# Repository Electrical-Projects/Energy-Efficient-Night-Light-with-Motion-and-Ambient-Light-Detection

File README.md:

## Energy-Efficient Night-Light with Motion and Ambient-Light Detection

# Description
A simple and affordable motion-activated LED circuit designed for environments where activation should depend on both motion and ambient light levels. The circuit uses a PIR motion sensor and a light-dependent resistor (LDR) to allow users to define the lighting conditions under which motion will trigger the LED. Two onboard potentiometers independently adjust: (1) the environmental light threshold (from full daylight to complete darkness) and (2) the LED on-time delay (0 – 72 seconds). The design is entirely analog, requiring no microcontroller, programming, or complex setup, making it easy to replicate and modify. The circuit is open source under GNU GPL 3.0 and may be freely used, modified, and shared.

# Overview
The system operates by combining PIR motion detection with ambient light sensing. The LDR and potentiometer form an adjustable voltage divider that biases a transistor, determining whether motion detection is enabled based on current light conditions. A TLV8544 low-power comparator stage processes the sensor signals and feeds them into a SN74LVC1G00 NAND gate for signal inversion and logic control before triggering a 555 timer configured in monostable mode. The second potentiometer adjusts the RC time constant of the 555 timer, allowing precise control over the LED on-time from near-instant to over one minute.

Most of the circuit is built with through-hole components for ease of assembly, modification, and long-term serviceability. The PIR sensor section, however, is a compact, self-contained module using mostly SMD components, as it continuously processes and conditions the sensor output — a task that benefits from a smaller, integrated, and more energy-efficient layout.

A series of resistors and filtering capacitors ensure noise immunity and stable operation even in fluctuating lighting or high-EMI environments. Bulk decoupling capacitors stabilize the 6 V nominal supply for reliable performance.

Unlike microcontroller-based solutions, this analog approach offers instant startup, minimal standby current, and long-term reliability without software maintenance. Potential applications include indoor lighting control, battery-powered motion lamps, and outdoor security lights with dusk-to-dawn control.

# Assembly & Modification
All necessary PCB design files, schematics, and a complete Bill of Materials (BOM) are included. Users can order parts directly from the BOM and have the PCB fabricated using the provided Gerber files. The prototype was entirely hand-soldered, using a mix of wire solder for through-hole components and solder paste for select SMD parts in the PIR section. The board includes outputs for two LEDs, allowing for multiple lighting configurations. Since all PCB design files are provided, users are free to modify layouts, adjust footprints, or expand the design for their own applications.

# Enclosure & Use Case
An enclosure design is included, sized to house the PCB and powered by four AAA batteries. In the reference build, this enclosure was used for an indoor novelty night light, shaped like a cat ornament, where the LEDs served as the cat’s eyes

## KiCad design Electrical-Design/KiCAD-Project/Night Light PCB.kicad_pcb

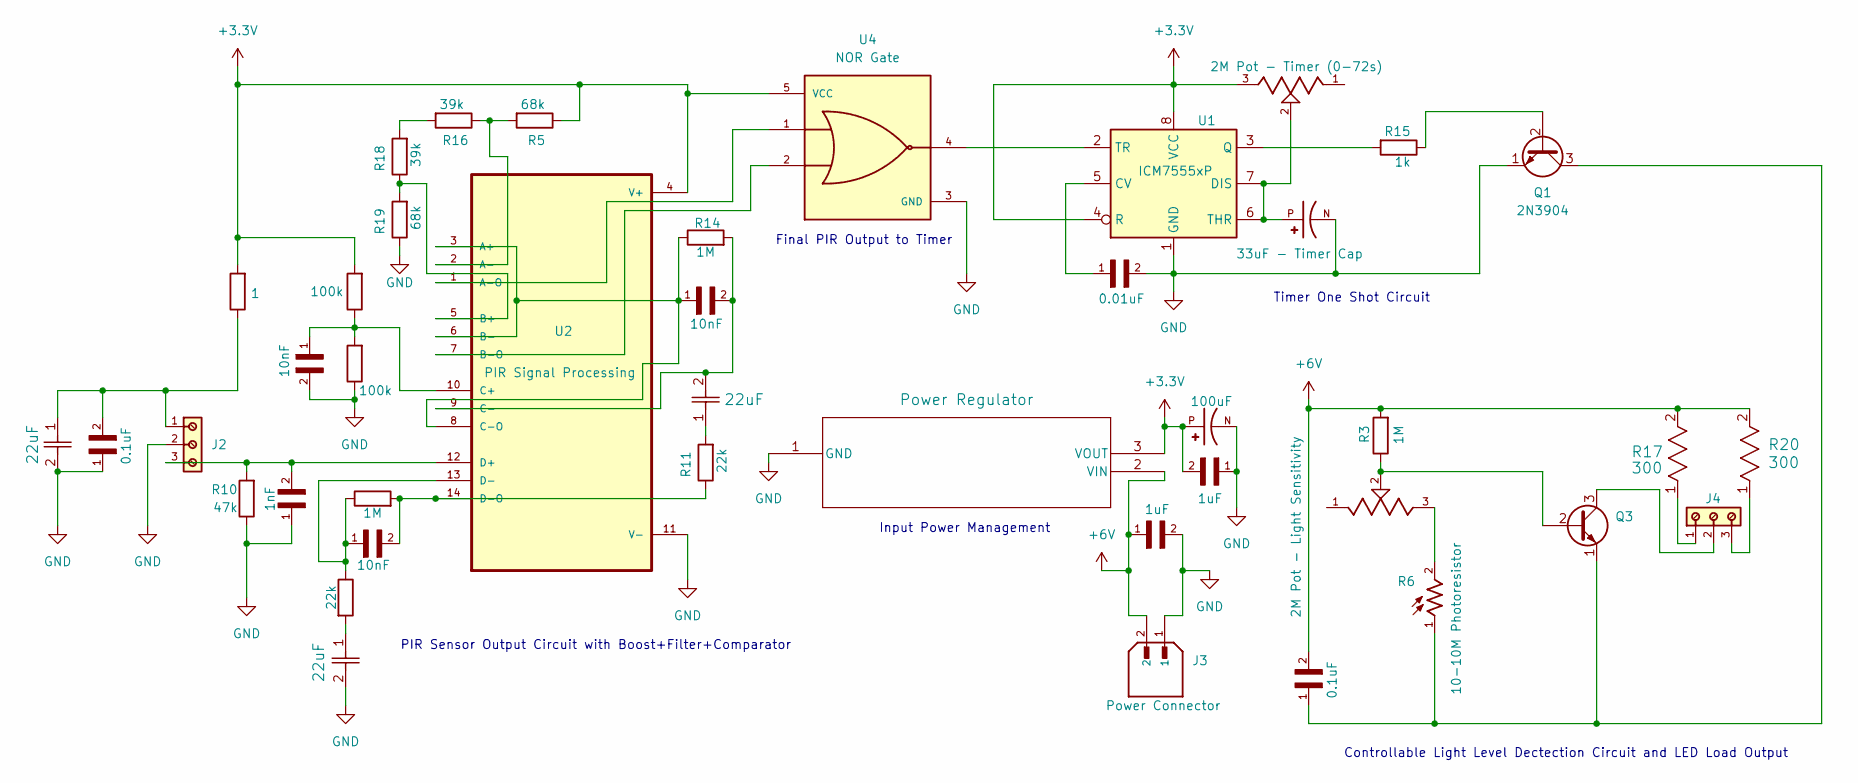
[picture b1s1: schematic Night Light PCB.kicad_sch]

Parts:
C1: 0.01uF; CAPRR254W54L381T254H466; PARTREV 12/14/2020
C2: 33uF - Timer Cap; CAPPRD350W60D800H1150; PARTREV 20-DEC-19
C3, C11: 22uF; FG20X7R1C226MRT06
C4: 100uF; CAPPRD250W45D630H700; PARTREV 28-FEB-20
C5, C13: 1uF; CAPRR254W54L381T254H466; PARTREV 12/14/2020
C6: 22uF; CAP_CL32_SAM-L
C7, C9, C10: 10nF; CAPRR254W54L381T254H466; PARTREV 12/14/2020
C8, C14: 0.1uF; CAPRR254W54L381T254H466; PARTREV 12/14/2020
C12: 1nF; CAPRR254W54L381T254H466; PARTREV 12/14/2020
J2, J4: 691214110003
J3: Power Connector; JST_B2B-XH-A; PARTREV N/A
Q1, Q3: 2N3904; TO-92_Inline
R3, R12, R14: 1M; R_1210_3225Metric_Pad1.30x2.65mm_HandSolder
R5, R19: 68k; R_1210_3225Metric_Pad1.30x2.65mm_HandSolder
R6: 10-10M Photoresistor; PHODET_PDV-P8103; PARTREV 3/30/06
R7: 1; R_1210_3225Metric_Pad1.30x2.65mm_HandSolder
R8, R9: 100k; R_1210_3225Metric_Pad1.30x2.65mm_HandSolder
R10: 47k; R_1210_3225Metric_Pad1.30x2.65mm_HandSolder
R11, R13: 22k; R_1210_3225Metric_Pad1.30x2.65mm_HandSolder
R15: 1k; R_1210_3225Metric_Pad1.30x2.65mm_HandSolder
R16, R18: 39k; R_1210_3225Metric_Pad1.30x2.65mm_HandSolder
R17, R20: 300; STA_RNMF14_STP
U1: ICM7555xP; DIP-8_W7.62mm
U2: PIR Signal Processing; SOIC127P600X175-14N
U3: Power Regulator; TO-92_MC_MCH
U4: NOR Gate; SOT95P280X145-5N; PARTREV X
VR2: 2M Pot - Timer (0-72s); TRIM_3314J-1-205E
VR3: 2M Pot - Light Sensitivity; TRIM_3314J-1-205E

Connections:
+3.3V: C4.P, C13.2, R5.1, R7.2, R8.2, U1.4 (R), U1.8 (VCC), U2.4 (V+), U3.3 (VOUT), U4.5 (VCC), VR2.3; also elsewhere on the board
+6V: C5.1, C14.2, J3.2, R3.2, R17.2, R20.2, U3.2 (VIN)
GND: C1.2, C2.N, C3.2, C4.N, C5.2, C8.1, C9.2, C11.2, C12.1, C13.1, J2.2, J3.1, Q1.1 (E), R9.1, R10.1, R19.1, U1.1 (GND), U2.11 (V-), U3.1 (GND), U4.3 (GND); also elsewhere on the board
unnamed: C3.1, C8.2, J2.1, R7.1
unnamed: C6.1, R11.2
unnamed: C11.1, R13.2
unnamed: J4.1, R17.1
unnamed: J4.3, R20.1
unnamed: Q1.2 (B), R15.1
unnamed: C14.1, Q1.3 (C), Q3.1 (E), R6.1
unnamed: Q3.2 (B), R3.1, VR3.2
unnamed: J4.2, Q3.3 (C)
unnamed: R6.2, VR3.3
unnamed: R16.2, R18.2
unnamed: C1.1, U1.5 (CV)
unnamed: C2.P, U1.6 (THR), U1.7 (DIS), VR2.2
unnamed: R15.2, U1.3 (Q)
unnamed: U1.2 (TR), U4.4
unnamed: C10.1, R14.1, U2.3 (A+), U2.6 (B-), U2.8 (C-O)
unnamed: R5.2, R16.1, U2.2 (A-)
unnamed: U2.1 (A-O), U4.1
unnamed: R18.1, R19.2, U2.5 (B+)
unnamed: U2.7 (B-O), U4.2
unnamed: C9.1, R8.1, R9.2, U2.10 (C+)
unnamed: C6.2, C10.2, R14.2, U2.9 (C-)
unnamed: C12.2, J2.3, R10.2, U2.12 (D+)
unnamed: C7.1, R12.1, R13.1, U2.13 (D-)
unnamed: C7.2, R11.1, R12.2, U2.14 (D-O)

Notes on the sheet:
PIR Sensor Output Circuit with Boost+Filter+Comparator
Controllable Light Level Dectection Circuit and LED Load Output
Final PIR Output to Timer
Input Power Management
Timer One Shot Circuit

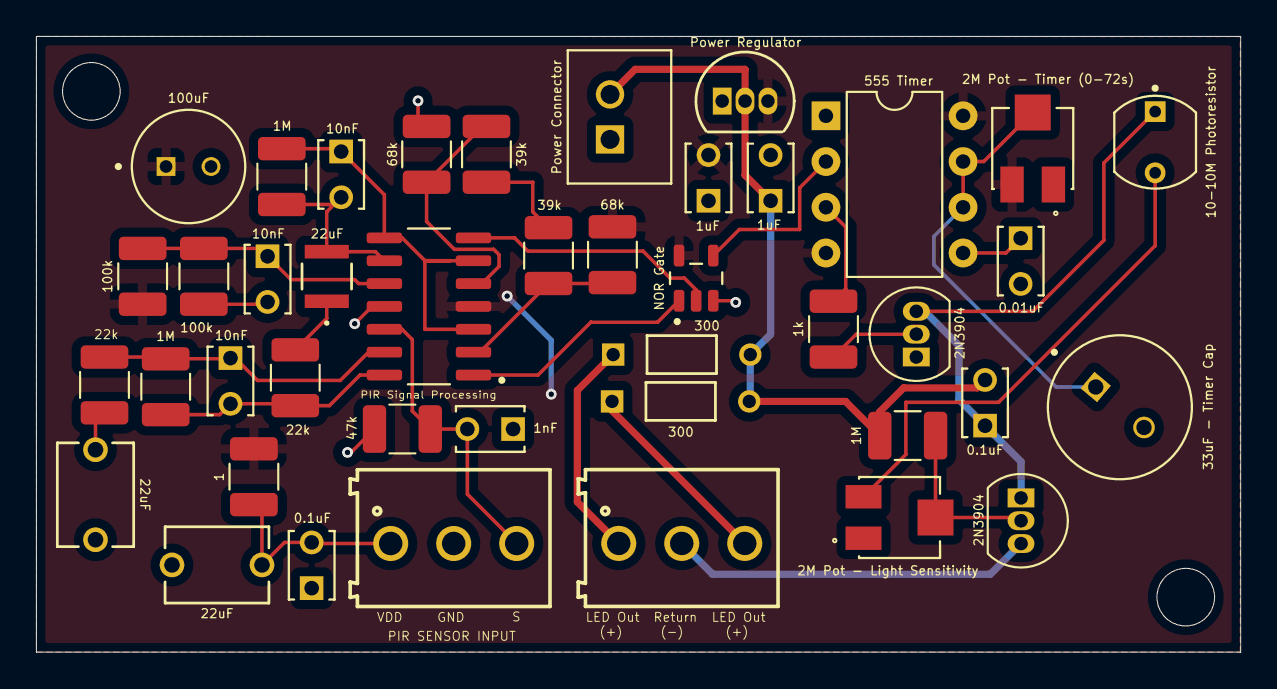
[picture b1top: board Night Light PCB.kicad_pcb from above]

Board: 2 copper layers, 66.9 x 34.2 mm, 42 parts (0 on the bottom side), 28 nets.

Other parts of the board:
100uF: EEAGA1A101; CAPPRD250W45D630H700

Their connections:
+3.3V: 100uF.P; also elsewhere on the board
GND: 100uF.N; also elsewhere on the board

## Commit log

2025-08-08 Create 3D-Printanble-STL
